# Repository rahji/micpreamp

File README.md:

# micpreamp
A microphone preamp that works well with piezo disc contact mics

It's based on the schematic (and comments) at [this Instructable](https://www.instructables.com/id/Guitar-Contact-Microphone-Preamp/). I designed the board to be all SMD and to sit underneath the long-lead PC-mount 1/4" stereo jacks. A nice detail is that it turns off when you disconnect a cable from the output jack, so there's no on-off switch for the unit. 

I made these for a workshop that I did at the Haystack Mountain School of Crafts, for the 2018 MassArt Alumni Retreat. I soldered all the SMD components beforehand and participants soldered the jacks and the battery snaps. Then they made contact mics from piezo discs that I supplied. These preamps worked great to get better sound out of the contact mics. I've included the files that I used to laser cut little boxes from lauan plywood scraps I had lying around. They fit tightly into the laser cut boxes with a 9V battery. 

## Bill of Materials

| Qty | Ref | Supplier        | Part                      | Link  |
|:---:|:---:|--------------- | ------------------------- | ----- |
| 2   | J1,J2 | All Electronics | PC Mount 1/4" Stereo Jack |  [SPHJ-12](https://www.allelectronics.com/item/sphj-12/stereo-1/4-phone-jack-pc-mount/1.html) |
| 1   |       | All Electronics | 9V Battery Snap I-Type    |  [BST-51](https://www.allelectronics.com/item/bst-51/9v-battery-snap-i-type/1.html) 
| 2   |       | Full Compass    | Neutrik NRJ-NUT-B Neutrik NRJ Jack Hex Nut | [NRJ-NUT-B](https://www.fullcompass.com/prod/119396-neutrik-nrj-nut-b-neutrik-nrj-jack-hex-nut) |
| 2   | C3,C4 | Arrow | Cap Aluminum Lytic 10uF 16V 20%  | [UWX1C100MCL1GB](https://www.arrow.com/en/products/uwx1c100mcl1gb/nichicon) |
| 2   | R5,R6 | Arrow | Res Thick Film 0805 22M Ohm 5% 0.25W  | [RK73B2ATTD226J](https://www.arrow.com/en/products/rk73b2attd226j/koa-speer-electronics) |
| 1   | R3    | Arrow | Res Thick Film 0805 10K Ohm 1% 0.125W  | [CRG0805F10K/10](https://www.arrow.com/en/products/crg0805f10k10/te-connectivity) |
| 1   | C2    | Arrow | Cap Ceramic 0.001uF (1nF) 50V X7R 5% SMD 0805  | [CL21B102JBANNNC](https://www.arrow.com/en/products/cl21b102jbannnc/samsung-electro-mechanics) |
| 1   | C1    | Arrow | Cap Ceramic 0.1uF 25V X7R 10% SMD 0805  | [08053C104KAT4A](https://www.arrow.com/en/products/08053c104kat4a/avx) |
| 1   | Q1 | Arrow | Trans JFET N-CH 25V 3-Pin SOT-23 T/R  | [MMBF5457](https://www.arrow.com/en/products/mmbf5457/on-semiconductor) |
| 1   | R2 | Arrow | Res Thick Film 0805 100K Ohm 1% 0.125W  | [RMCF0805FG100K](https://www.arrow.com/en/products/rmcf0805fg100k/stackpole-electronics) |

The jacks seem like surplus from All Electronics and are pretty particular, so hopefully you can still get them as you read this. They didn't include the nuts, so I had to find those at from a different supplier. Check with me before you buy parts - I might have extra parts or even a fully assembled unit.

You could experiment with leaving out C1, C2, and/or C3, but I used them on the boards I made. If you left out C1, you'd have to jump its pads by making a solder bridge between them. The same goes for C3, but since the gap is larger for that capacitor, I left a solder-jumper on the board. You could play around with these variables or just include all the parts as I did, since they cost pennies.

## Assembly

You can order the PCB from OSH Park by [uploading the file directly from here](https://oshpark.com/import?url=https://raw.githubusercontent.com/rahji/micpreamp/master/eagle/smd_preamp_with_TALL_jacks.brd). You'll get three boards for the price that they show. A couple notes about soldering the components to the board: First, everything is soldered on the *top* side of the board. Obviously the jacks go on last (since most of the other components are underneath the jacks). It's okay to solder the battery snap leads on after the jacks, though. Second: Even though I added thermals where the 10uF caps get soldered to the ground plane, it's difficult to get the heat right if you're soldering by hand. This might be a good project with which to hone your hot plate, toaster oven, hot air reflow, or other techniques, rather than soldering with an iron. 🤷🏽‍♂️

Have fun :)

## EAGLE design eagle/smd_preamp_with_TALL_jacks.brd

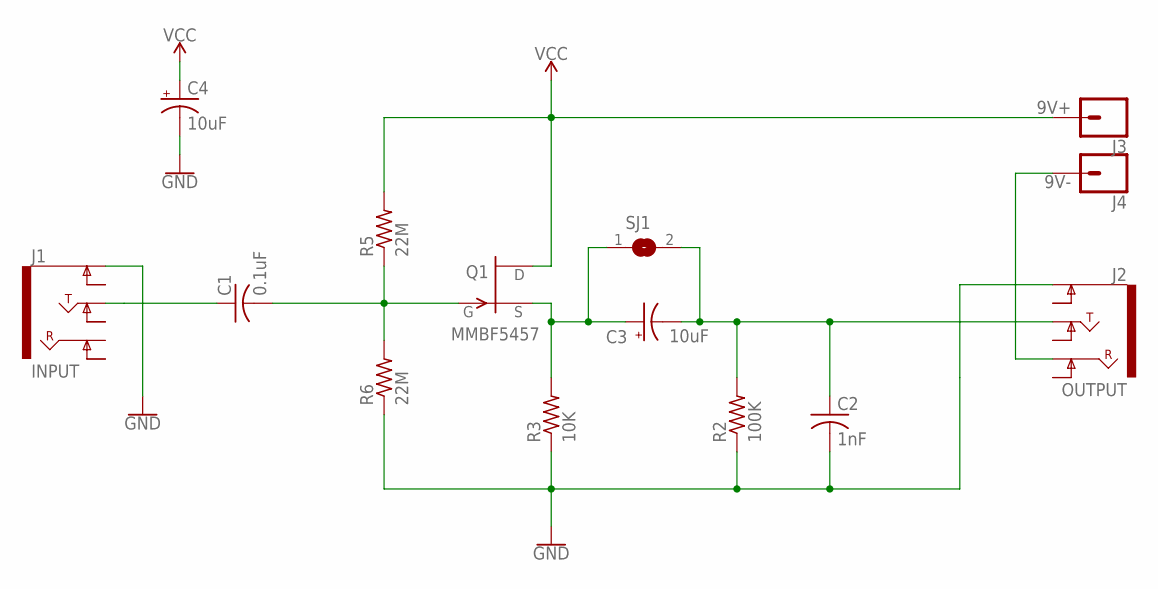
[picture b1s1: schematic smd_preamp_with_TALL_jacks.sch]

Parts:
C1: 0.1uF; C0805
C2: 1nF; C0805
C3, C4: 10uF; 732-8411-1-ND_SMD
J1: INPUT; CLIFF_AUDIO_JACK_0.25"_TRS_PTH_RA
J2: OUTPUT; CLIFF_AUDIO_JACK_0.25"_TRS_PTH_RA
J3: 9V+; 1X01
J4: 9V-; 1X01
Q1: MMBF5457; SOT23
R2: 100K; R0805
R3: 10K; R0805
R5, R6: 22M; R0805
SJ1: SJ

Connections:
GATE: C1.2, Q1.3 (G), R5.1, R6.2
GND: C2.2, C4.-, J1.SLEEVE (EARTH), J2.SLEEVE (EARTH), R2.1, R3.1, R6.1
unnamed: C1.1, J1.TIP
unnamed: J2.RING, J4.1
unnamed: C2.1, C3.-, J2.TIP, R2.2, SJ1.2
SOURCE: C3.+, Q1.2 (S), R3.2, SJ1.1
VCC: C4.+, J3.1, Q1.1 (D), R5.2

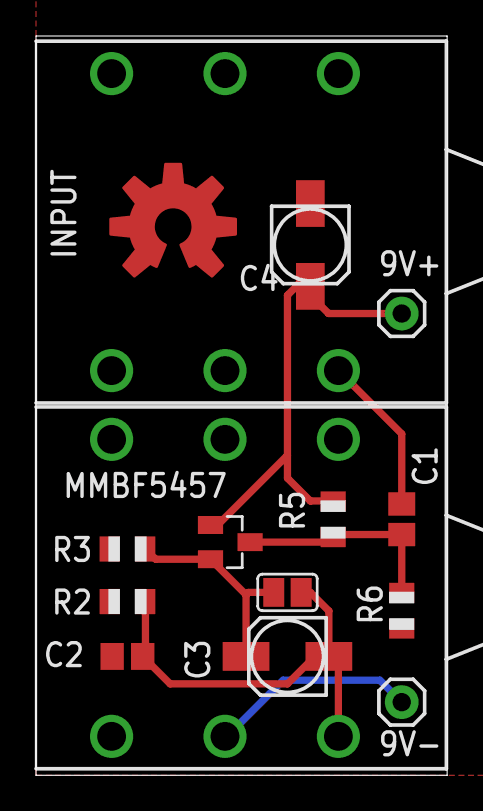
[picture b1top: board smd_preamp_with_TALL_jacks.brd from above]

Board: 2 copper layers, 22.8 x 41.1 mm, 15 parts (0 on the bottom side), 7 nets.

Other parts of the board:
U$1: OSHW-LOGO-L_COPPER

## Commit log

2018-09-20 Rename smd_preamp_with_TALL_jacks_CREAM.dxf to preamp_cream_layer_export.dxf
2018-09-20 Commit box files
2018-09-20 Organize files into folders
2018-09-20 Removing duplicate files
2018-09-24 Uploading Illustrator CS5 box file for lasering
2019-04-26 Made a proper readme
2019-04-26 added images for schematic and pcb layout
2019-04-26 Added schematic to readme

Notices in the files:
parts and their libraries:
SparkFun-Connectors: Licensing: Creative Commons ShareAlike 4.0 International - https://creativecommons.org/licenses/by-sa/4.0
